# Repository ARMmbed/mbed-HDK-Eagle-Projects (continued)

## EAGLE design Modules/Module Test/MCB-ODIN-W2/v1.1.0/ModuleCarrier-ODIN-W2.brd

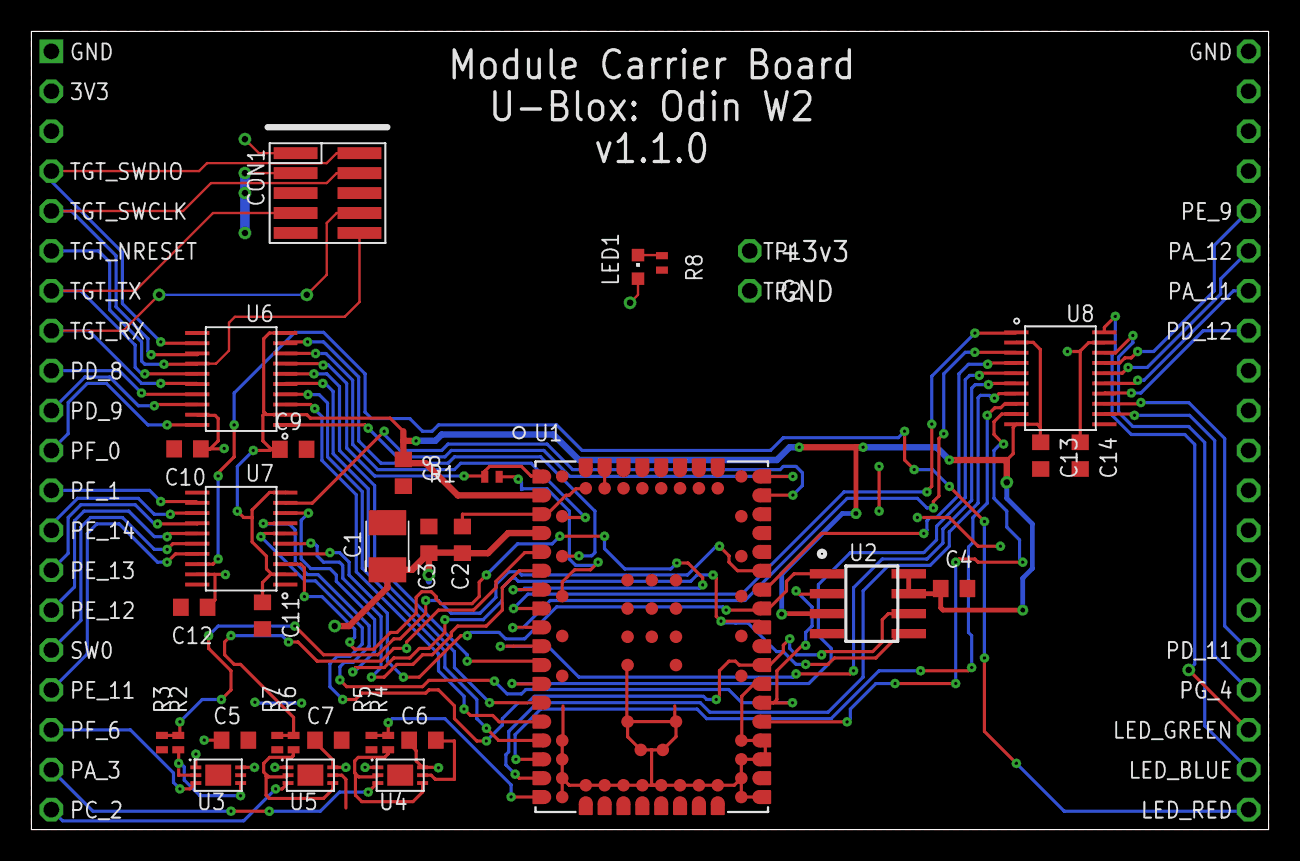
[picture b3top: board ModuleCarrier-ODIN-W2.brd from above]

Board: 2 copper layers, 78.7 x 50.8 mm, 35 parts (0 on the bottom side), 60 nets.

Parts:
C1: 10uF; SMC_B
C2, C3, C4, C5, C6, C7, C8, C9, C10, C11, C12, C13, C14: 100nF; 0603
CON1: SWD-10/TC2050_SMD; FTSH-105-02
LED1: RED; CHIPLED_0603
R1: 0; 0402
R2, R4, R6: 10K; 0402
R3, R5, R7: 12K; 0402
R8: 1k; 0402
TP1, TP2: TEST-POINT-50R-PTH; TP50-PTH
U1: ODIN-W262; ODIN-88
U2: MX25R3235FM1IH0; SO8
U3, U4, U5: LT6000IDCB#TRMPBF; 6-DFN
U6, U7, U8: TXS0108EPWR; TSSOP-20
U$1: MODULE_DAUGHTER

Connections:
1.8V: C4.2, C8.1, C9.1, C11.1, C13.1, U1.A2, U2.3, U2.7, U2.8, U6.2, U6.10, U7.2, U7.10, U8.2, U8.10
3V3-LED_BLUE: U8.18, U$1.22
3V3-LED_GREEN: U8.20, U$1.23
3V3-LED_RED: U7.18, U$1.21
3V3-PA_11: U8.15, U$1.34
3V3-PA_12: U8.16, U$1.35
3V3-PD_8: U6.17, U$1.9
3V3-PD_9: U6.18, U$1.10
3V3-PD_11: U8.13, U$1.25
3V3-PD_12: U8.14, U$1.33
3V3-PE_9: U8.17, U$1.36
3V3-PE_11: U7.17, U$1.17
3V3-PE_12: U7.15, U$1.15
3V3-PE_13: U7.14, U$1.14
3V3-PE_14: U7.13, U$1.13
3V3-PF_0: U6.20, U$1.11
3V3-PF_1: U7.12, U$1.12
3V3-PG_4: U8.12, U$1.24
3V3-SW0: U7.16, U$1.16
3V3-TGT_NRESET: CON1.10, U6.14, U$1.6
3V3-TGT_RX: CON1.8, U6.16, U$1.8
3V3-TGT_SWCLK: CON1.4, U6.13, U$1.5
3V3-TGT_SWDIO: CON1.2, U6.12, U$1.4
3V3-TGT_TX: CON1.7, U6.15, U$1.7
+3.3V: C1.+, C2.1, C3.1, C5.1, C6.1, C7.1, C10.1, C12.1, C14.1, CON1.1, LED1.A, TP1.TP, U1.A4, U3.1, U3.6, U4.1, U4.6, U5.1, U5.6, U6.19, U7.19, U8.19, U$1.2
A0_3V3: U3.3, U$1.18
A1_3V3: U4.3, U$1.19
A2_3V3: U5.3, U$1.20
GND: C1.-, C2.2, C3.2, C4.1, C5.2, C6.2, C7.2, C8.2, C9.2, C10.2, C11.2, C12.2, C13.2, C14.2, CON1.3, CON1.5, CON1.9, R3.1, R5.1, R7.1, R8.1, TP2.TP, U1.1, U1.2, U1.3, U1.4, U1.5, U1.6, U1.7, U1.8, U1.9, U1.10, U1.11, U1.12, U1.13, U1.14, U1.15, U1.16, U1.17, U1.18, U1.19, U1.20, U1.21, U1.22, U1.23, U1.24, U1.25, U1.26, U1.27, U1.28, U1.29, U1.30, U1.31, U1.32, U1.33, U1.34, U1.35, U1.36, U1.37, U1.38, U1.39, U1.A3, U1.C1, U1.C3, U1.C4, U1.C7, U1.D7, U2.4, U3.5, U3.P$7, U4.5, U4.P$7, U5.5, U5.P$7, U6.11, U7.11, U8.11, U$1.1, U$1.40
LED_BLUE: U1.A9, U8.3
LED_GREEN: U1.A8, U8.1
LED_RED: U1.A7, U7.3
unnamed: R1.2, U1.TP5
unnamed: R2.1, U3.2, U3.4
unnamed: R4.1, U4.2, U4.4
unnamed: R6.1, U5.2, U5.4
PA_1: LED1.C, R8.2
PA_3: R4.2, R5.2, U1.A18
PA_11: U1.A10, U8.6
PA_12: U1.A12, U8.5
PC_2: R6.2, R7.2, U1.A5
PD_8: U1.A15, U6.4
PD_9: U1.A14, U6.3
PD_11: U1.A16, U8.8
PD_12: U1.A17, U8.7
PE_9: U1.C12, U8.4
PE_11: U1.C11, U2.1, U7.4
PE_12: U1.C8, U2.6, U7.6
PE_13: U1.C6, U2.2, U7.7
PE_14: U1.C10, U2.5, U7.8
PF_0: U1.C18, U6.1
PF_1: U1.C17, U7.9
PF_6: R2.2, R3.2, U1.C13
PG_4: U1.C5, U8.9
SW0: U1.A6, U7.5
TGT_NRESET: R1.1, U1.A1, U6.7
TGT_RX: U1.A13, U6.5
TGT_SWCLK: U1.TP9, U6.8
TGT_SWDIO: U1.TP7, U6.9
TGT_TX: U1.A11, U6.6

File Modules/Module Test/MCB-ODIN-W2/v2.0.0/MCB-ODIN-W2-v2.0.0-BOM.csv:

"Qty";"Value";"Device";"Package";"Parts";"Description";"MF";"MFN";"OC-DIGIKEY";"OC-MOUSER";"OC-NEWARK";
"1";"0";"RESISTOR0402";"0402";"R1";"Resistor";"";"";"";"";"";
"14";"100nF";"C0603";"0603";"C2, C3, C4, C5, C6, C7, C8, C9, C10, C11, C12, C13, C14, C24";"Capacitor";"";"";"";"";"";
"3";"10K";"R0603";"0603";"R2, R4, R6";"Resistor";"";"";"";"";"";
"1";"10uF";"C-POLB";"SMC_B";"C1";"Polarised capacitor";"Kemet";"T491B106K020AT";"399-8298-1-ND";"80-T491B106K020";" 57K1740";
"3";"12K";"R0603";"0603";"R3, R5, R7";"Resistor";"";"";"";"";"";
"1";"1k";"R0603";"0603";"R8";"Resistor";"";"";"";"";"";
"2";"4k7";"R0603";"0603";"R10, R11";"Resistor";"";"";"";"";"";
"1";"ATECC608A";"ATECC608A";"SO8";"IC3";"I2C Secure element and crytpo accelerator";"Atmel";"ATECC608A";"ATECC608A-SSHDA-TCT-ND ";"556-ATECC608ASSHDAB ";"";
"1";"GREEN";"SMD_LED0603";"CHIPLED_0603";"LED1";"LED SMD, Colour Red";"Wurth Electronics Inc";"150060RS75000";"732-4978-1-ND";"710-150060RS75000";"2322071";
"3";"LT6000IDCB#TRMPBF";"LT6000IDCB#TRMPBF";"6-DFN";"U3, U4, U5";"IC OPAMP GBP 60KHZ RRO 6DFN";"Linear Technology";"LT6000IDCB#TRMPBF";"LT6000IDCB#TRMPBFCT-ND";"";"95M6567";
"1";"MODULE_DAUGHTER";"MODULE_DAUGHTER";"MODULE_DAUGHTER";"MOD1";"";"";"";"";"";"";
"1";"MX25R3235FM1IH0";"MX25R3235FM1IH0";"SO8";"U2";"Serial Flash 32 Mb 80 Mhz";"Macronix";"MX25R3235FM2IH0";"1092-1174-ND";"";"";
"1";"ODIN-W262";"ODIN-W262";"ODIN-88";"U1";"ODIN-W260: Host-based multiradio module with";"";"";"";"";"";
"1";"SWD-10/TC2050_SMD";"SWD-10/TC2050_SMD";"FTSH-105-02";"CON1";"1mm pitch 10-Pin Cortex Programming Header with optional TC2050 footprint solderless interchangeable";"";"";"";"";"";
"2";"TEST_POINT-50R-PTH";"TEST_POINT-50R-PTH";"TP50-PTH";"TP1, TP2";"";"";"";"";"";"";
"3";"TXS0108EPWR";"TXS0108EPWR";"TSSOP-20";"U6, U7, U8";"8-Bit Bi-directional, Level-Shifting, Voltage Translator";"Texas Instruments";"TXS0108EPWR";"296-23011-1-ND";"595-TXS0108EPWR";"05R8300";

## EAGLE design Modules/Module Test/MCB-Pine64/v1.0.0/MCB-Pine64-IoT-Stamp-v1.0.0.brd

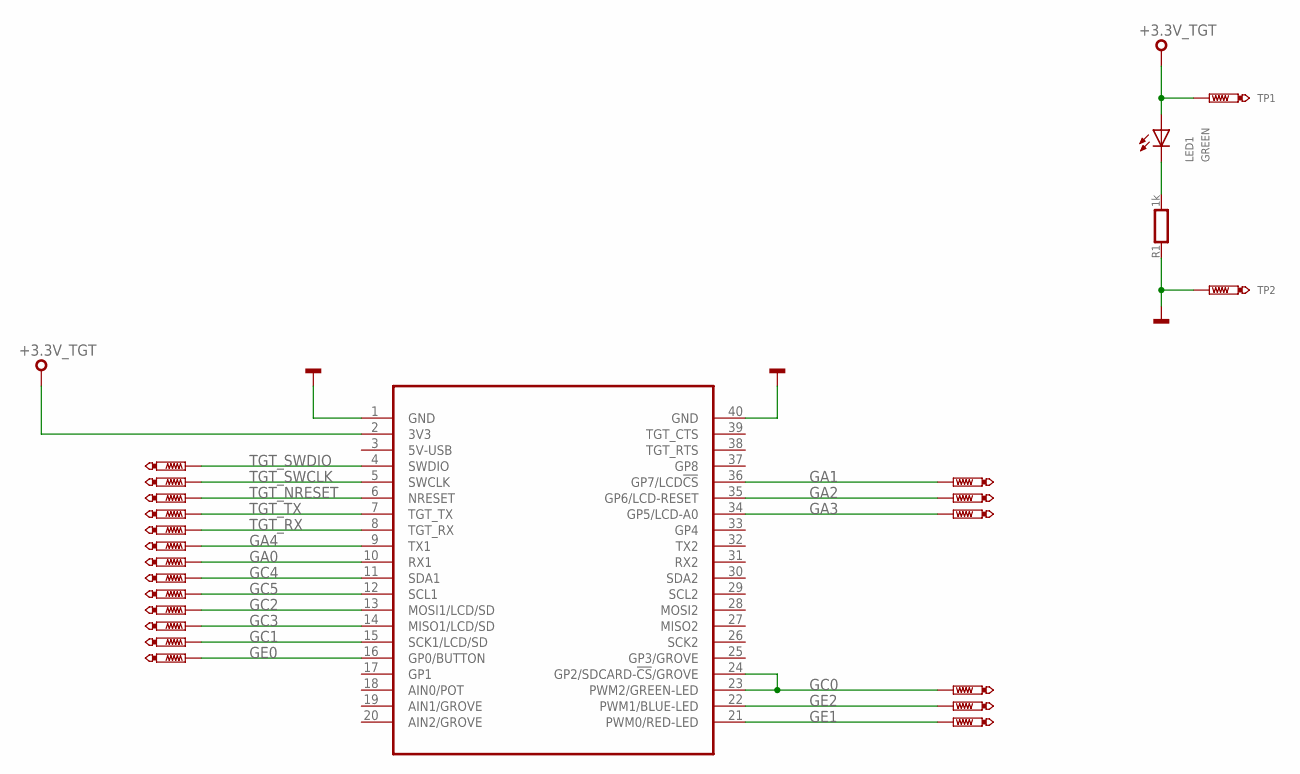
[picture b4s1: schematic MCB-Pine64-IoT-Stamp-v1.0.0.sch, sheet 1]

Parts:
LED1: GREEN; CHIPLED_0603
MOD1: MODULE_DAUGHTER
R1: 1k; 0603
TP1, TP2: TEST-POINT-50R-PTH; TP50-PTH
TP3, TP4, TP7, TP8, TP9, TP13, TP14, TP15, TP17, TP19, TP20, TP21, TP22, TP25, TP26, TP27, TP28, TP29, TP30: PTR1TP07R; TP07R

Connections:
+3.3V_TGT: LED1.A, MOD1.2 (3V3), TP1.TP; also elsewhere on the board
GA0: MOD1.10 (RX1), TP21.TP; also elsewhere on the board
GA1: MOD1.36 (GP7/LCD!CS), TP25.TP; also elsewhere on the board
GA2: MOD1.35 (GP6/LCD-RESET), TP20.TP; also elsewhere on the board
GA3: MOD1.34 (GP5/LCD-A0), TP19.TP; also elsewhere on the board
GA4: MOD1.9 (TX1), TP22.TP; also elsewhere on the board
GC0: MOD1.23 (PWM2/GREEN-LED), MOD1.24 (GP2/SDCARD-!CS!/GROVE), TP15.TP; also elsewhere on the board
GC1: MOD1.15 (SCK1/LCD/SD), TP9.TP; also elsewhere on the board
GC2: MOD1.13 (MOSI1/LCD/SD), TP7.TP; also elsewhere on the board
GC3: MOD1.14 (MISO1/LCD/SD), TP8.TP; also elsewhere on the board
GC4: MOD1.11 (SDA1), TP3.TP; also elsewhere on the board
GC5: MOD1.12 (SCL1), TP4.TP; also elsewhere on the board
GE0: MOD1.16 (GP0/BUTTON), TP17.TP; also elsewhere on the board
GE1: MOD1.21 (PWM0/RED-LED), TP13.TP; also elsewhere on the board
GE2: MOD1.22 (PWM1/BLUE-LED), TP14.TP; also elsewhere on the board
GND: MOD1.1 (GND), MOD1.40 (GND), R1.1, TP2.TP; also elsewhere on the board
PA_1: LED1.C, R1.2
TGT_NRESET: MOD1.6 (NRESET), TP28.TP; also elsewhere on the board
TGT_RX: MOD1.8 (TGT_RX), TP30.TP; also elsewhere on the board
TGT_SWCLK: MOD1.5 (SWCLK), TP27.TP; also elsewhere on the board
TGT_SWDIO: MOD1.4 (SWDIO), TP26.TP; also elsewhere on the board
TGT_TX: MOD1.7 (TGT_TX), TP29.TP; also elsewhere on the board

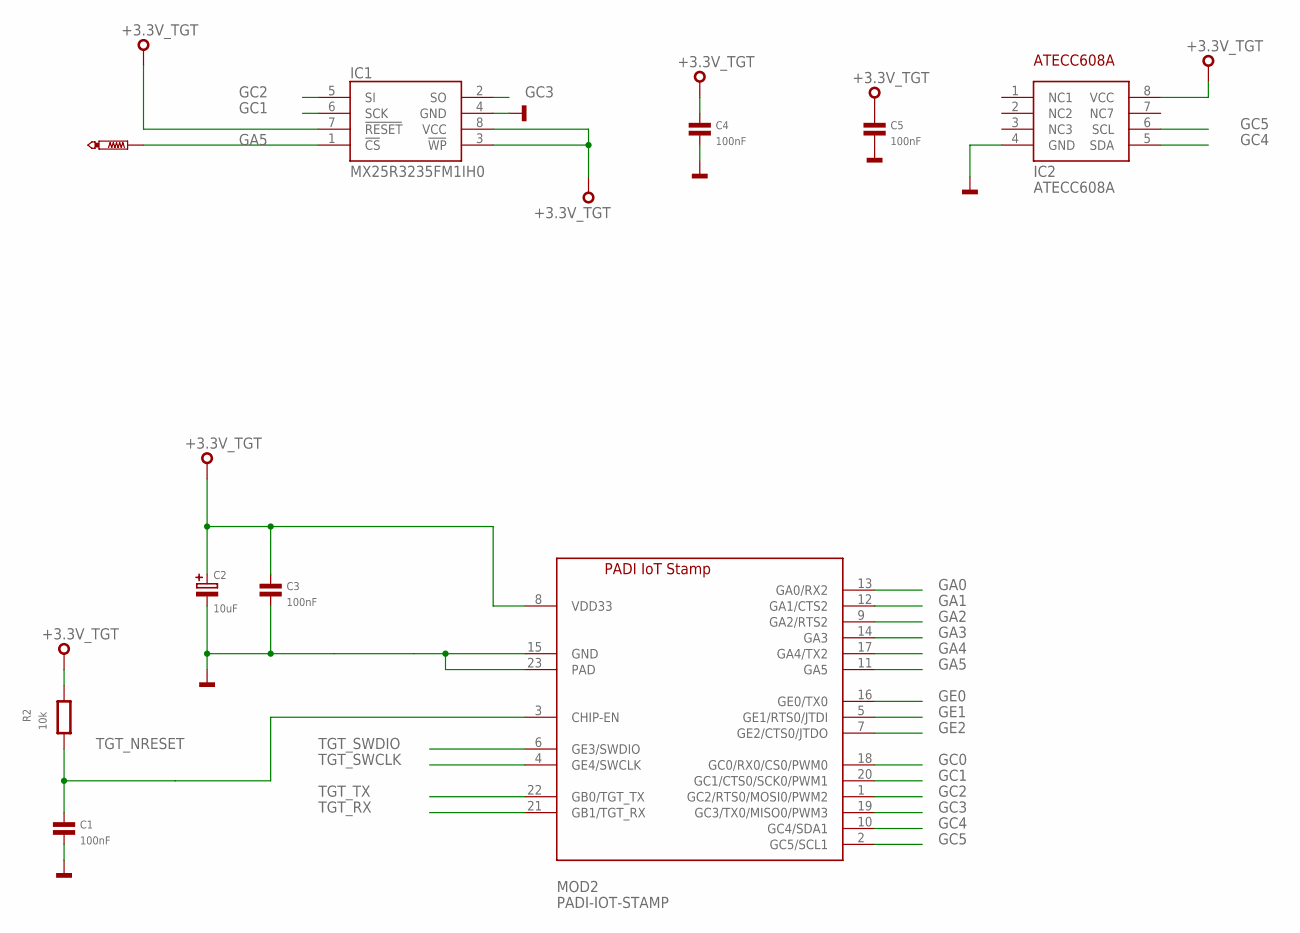
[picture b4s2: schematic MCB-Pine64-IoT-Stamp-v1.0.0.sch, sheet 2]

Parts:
C1, C3, C4, C5: 100nF; 0603
C2: 10uF; SMC_B
IC1: MX25R3235FM1IH0; SO8
IC2: ATECC608A; SO8
MOD2: PADI-IOT-STAMP
R2: 10k; 0603
TP5: PTR1TP07R; TP07R

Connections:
+3.3V_TGT: C2.+, C3.1, C4.1, C5.1, IC1.3 (!WP), IC1.7 (!RESET), IC1.8 (VCC), IC2.8 (VCC), MOD2.8 (VDD33), R2.2; also elsewhere on the board
GA0: MOD2.13 (GA0/RX2); also elsewhere on the board
GA1: MOD2.12 (GA1/CTS2); also elsewhere on the board
GA2: MOD2.9 (GA2/RTS2); also elsewhere on the board
GA3: MOD2.14 (GA3); also elsewhere on the board
GA4: MOD2.17 (GA4/TX2); also elsewhere on the board
GA5: IC1.1 (!CS), MOD2.11 (GA5), TP5.TP
GC0: MOD2.18 (GC0/RX0/CS0/PWM0); also elsewhere on the board
GC1: IC1.6 (SCK), MOD2.20 (GC1/CTS0/SCK0/PWM1); also elsewhere on the board
GC2: IC1.5 (SI), MOD2.1 (GC2/RTS0/MOSI0/PWM2); also elsewhere on the board
GC3: IC1.2 (SO), MOD2.19 (GC3/TX0/MISO0/PWM3); also elsewhere on the board
GC4: IC2.5 (SDA), MOD2.10 (GC4/SDA1); also elsewhere on the board
GC5: IC2.6 (SCL), MOD2.2 (GC5/SCL1); also elsewhere on the board
GE0: MOD2.16 (GE0/TX0); also elsewhere on the board
GE1: MOD2.5 (GE1/RTS0/JTDI); also elsewhere on the board
GE2: MOD2.7 (GE2/CTS0/JTDO); also elsewhere on the board
GND: C1.2, C2.-, C3.2, C4.2, C5.2, IC1.4 (GND), IC2.4 (GND), MOD2.15 (GND), MOD2.23 (PAD); also elsewhere on the board
TGT_NRESET: C1.1, MOD2.3 (CHIP-EN), R2.1; also elsewhere on the board
TGT_RX: MOD2.21 (GB1/TGT_RX); also elsewhere on the board
TGT_SWCLK: MOD2.4 (GE4/SWCLK); also elsewhere on the board
TGT_SWDIO: MOD2.6 (GE3/SWDIO); also elsewhere on the board
TGT_TX: MOD2.22 (GB0/TGT_TX); also elsewhere on the board

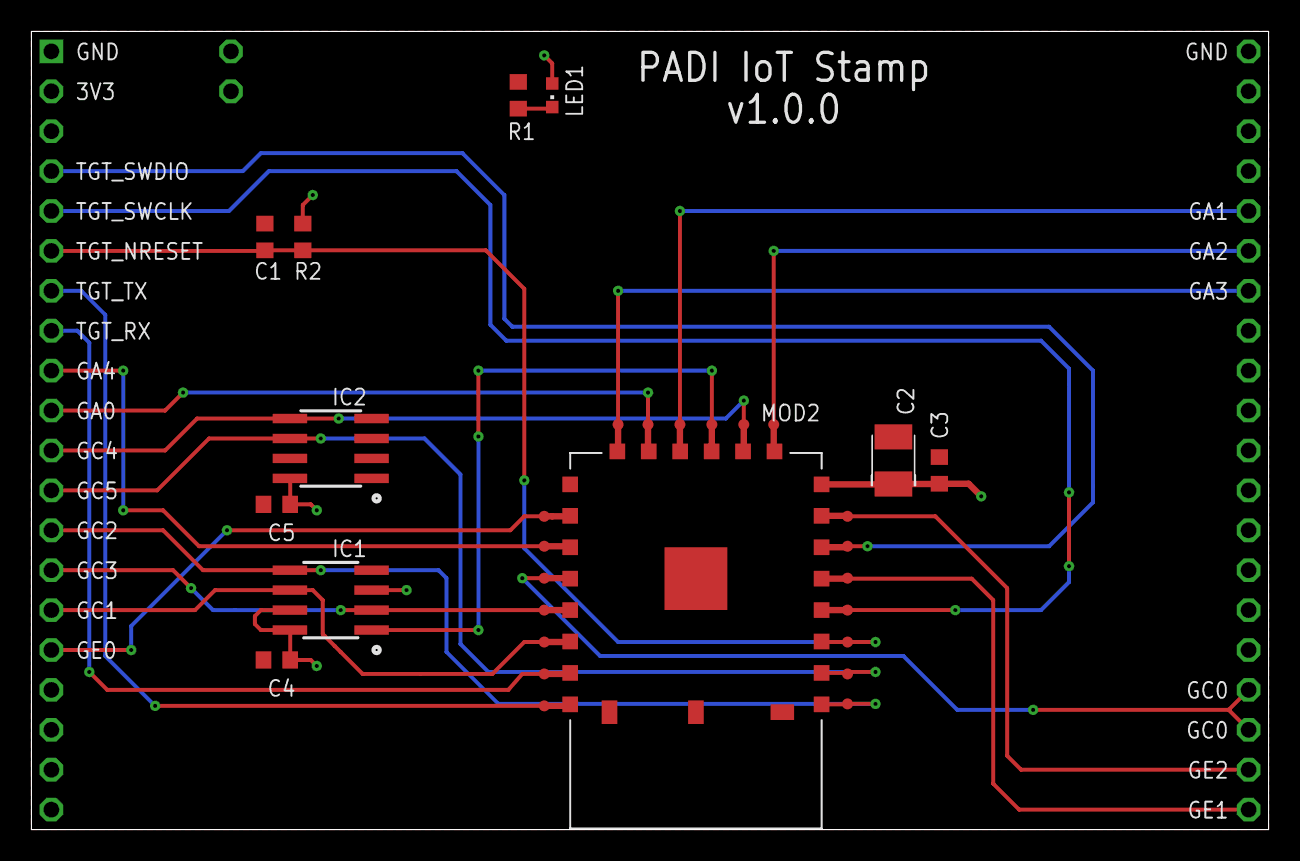
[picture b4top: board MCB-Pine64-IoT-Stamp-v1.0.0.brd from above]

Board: 2 copper layers, 78.7 x 50.8 mm, 35 parts (0 on the bottom side), 23 nets.

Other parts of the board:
SS2: FLOSSICORN0.25; FLOSSICORN-0.25

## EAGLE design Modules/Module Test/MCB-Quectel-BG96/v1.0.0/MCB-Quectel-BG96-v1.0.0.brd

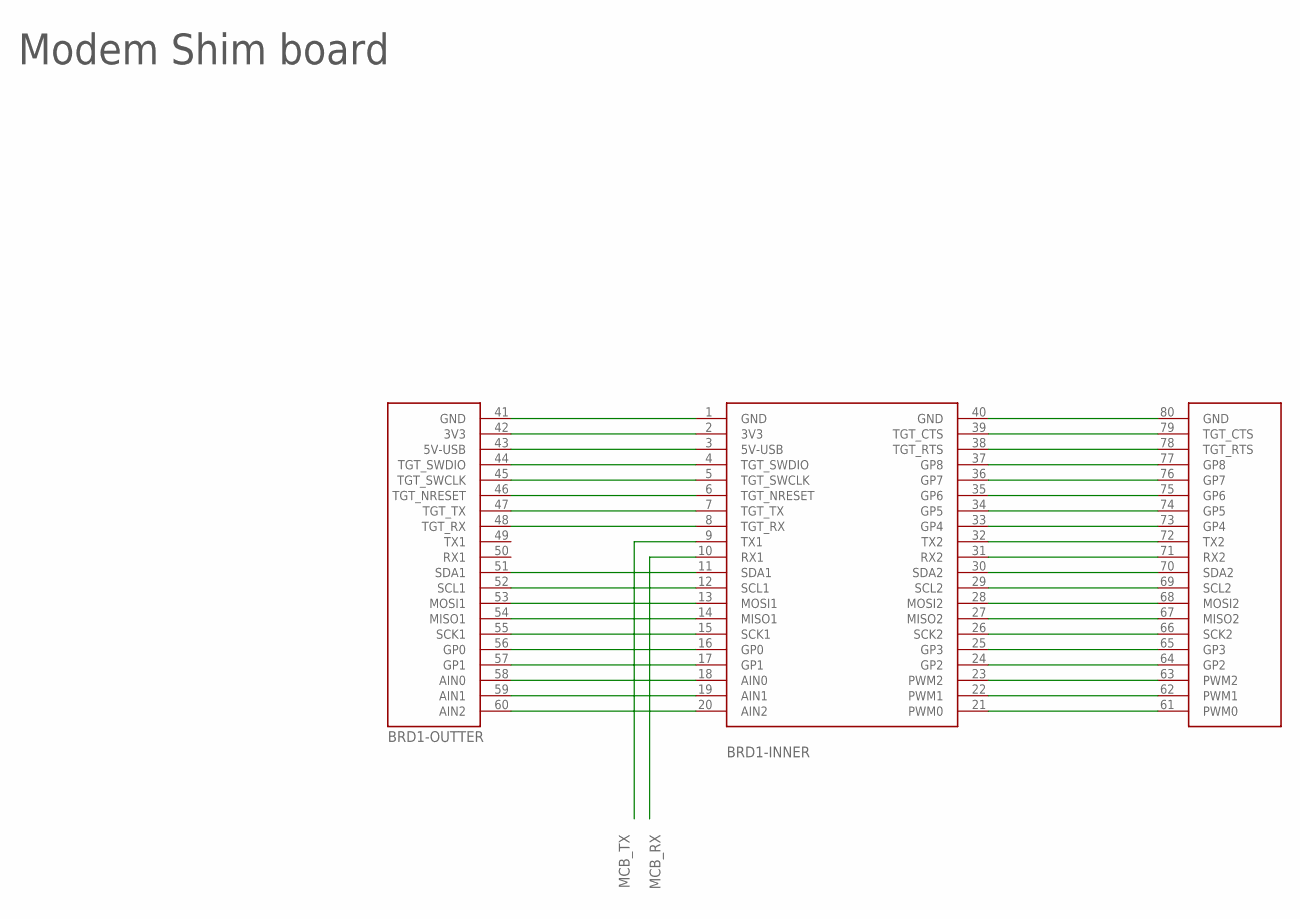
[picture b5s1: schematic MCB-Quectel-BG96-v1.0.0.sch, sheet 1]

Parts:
BRD1: MODULE-SHIM-BRD; MODULE-SHIM-BOARD

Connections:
MCB_RX: BRD1.10 (RX1)
MCB_TX: BRD1.9 (TX1)
unnamed: BRD1.40 (GND), BRD1.80 (GND)
unnamed: BRD1.39 (TGT_CTS), BRD1.79 (TGT_CTS)
unnamed: BRD1.38 (TGT_RTS), BRD1.78 (TGT_RTS)
unnamed: BRD1.37 (GP8), BRD1.77 (GP8)
unnamed: BRD1.36 (GP7), BRD1.76 (GP7)
unnamed: BRD1.35 (GP6), BRD1.75 (GP6)
unnamed: BRD1.34 (GP5), BRD1.74 (GP5)
unnamed: BRD1.33 (GP4), BRD1.73 (GP4)
unnamed: BRD1.32 (TX2), BRD1.72 (TX2)
unnamed: BRD1.31 (RX2), BRD1.71 (RX2)
unnamed: BRD1.30 (SDA2), BRD1.70 (SDA2)
unnamed: BRD1.29 (SCL2), BRD1.69 (SCL2)
unnamed: BRD1.28 (MOSI2), BRD1.68 (MOSI2)
unnamed: BRD1.27 (MISO2), BRD1.67 (MISO2)
unnamed: BRD1.26 (SCK2), BRD1.66 (SCK2)
unnamed: BRD1.25 (GP3), BRD1.65 (GP3)
unnamed: BRD1.24 (GP2), BRD1.64 (GP2)
unnamed: BRD1.23 (PWM2), BRD1.63 (PWM2)
unnamed: BRD1.22 (PWM1), BRD1.62 (PWM1)
unnamed: BRD1.21 (PWM0), BRD1.61 (PWM0)
unnamed: BRD1.1 (GND), BRD1.41 (GND)
unnamed: BRD1.2 (3V3), BRD1.42 (3V3)
unnamed: BRD1.3 (5V-USB), BRD1.43 (5V-USB)
unnamed: BRD1.4 (TGT_SWDIO), BRD1.44 (TGT_SWDIO)
unnamed: BRD1.5 (TGT_SWCLK), BRD1.45 (TGT_SWCLK)
unnamed: BRD1.6 (TGT_NRESET), BRD1.46 (TGT_NRESET)
unnamed: BRD1.7 (TGT_TX), BRD1.47 (TGT_TX)
unnamed: BRD1.8 (TGT_RX), BRD1.48 (TGT_RX)
unnamed: BRD1.11 (SDA1), BRD1.51 (SDA1)
unnamed: BRD1.12 (SCL1), BRD1.52 (SCL1)
unnamed: BRD1.13 (MOSI1), BRD1.53 (MOSI1)
unnamed: BRD1.14 (MISO1), BRD1.54 (MISO1)
unnamed: BRD1.15 (SCK1), BRD1.55 (SCK1)
unnamed: BRD1.16 (GP0), BRD1.56 (GP0)
unnamed: BRD1.17 (GP1), BRD1.57 (GP1)
unnamed: BRD1.18 (AIN0), BRD1.58 (AIN0)
unnamed: BRD1.19 (AIN1), BRD1.59 (AIN1)
unnamed: BRD1.20 (AIN2), BRD1.60 (AIN2)

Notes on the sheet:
Modem Shim board

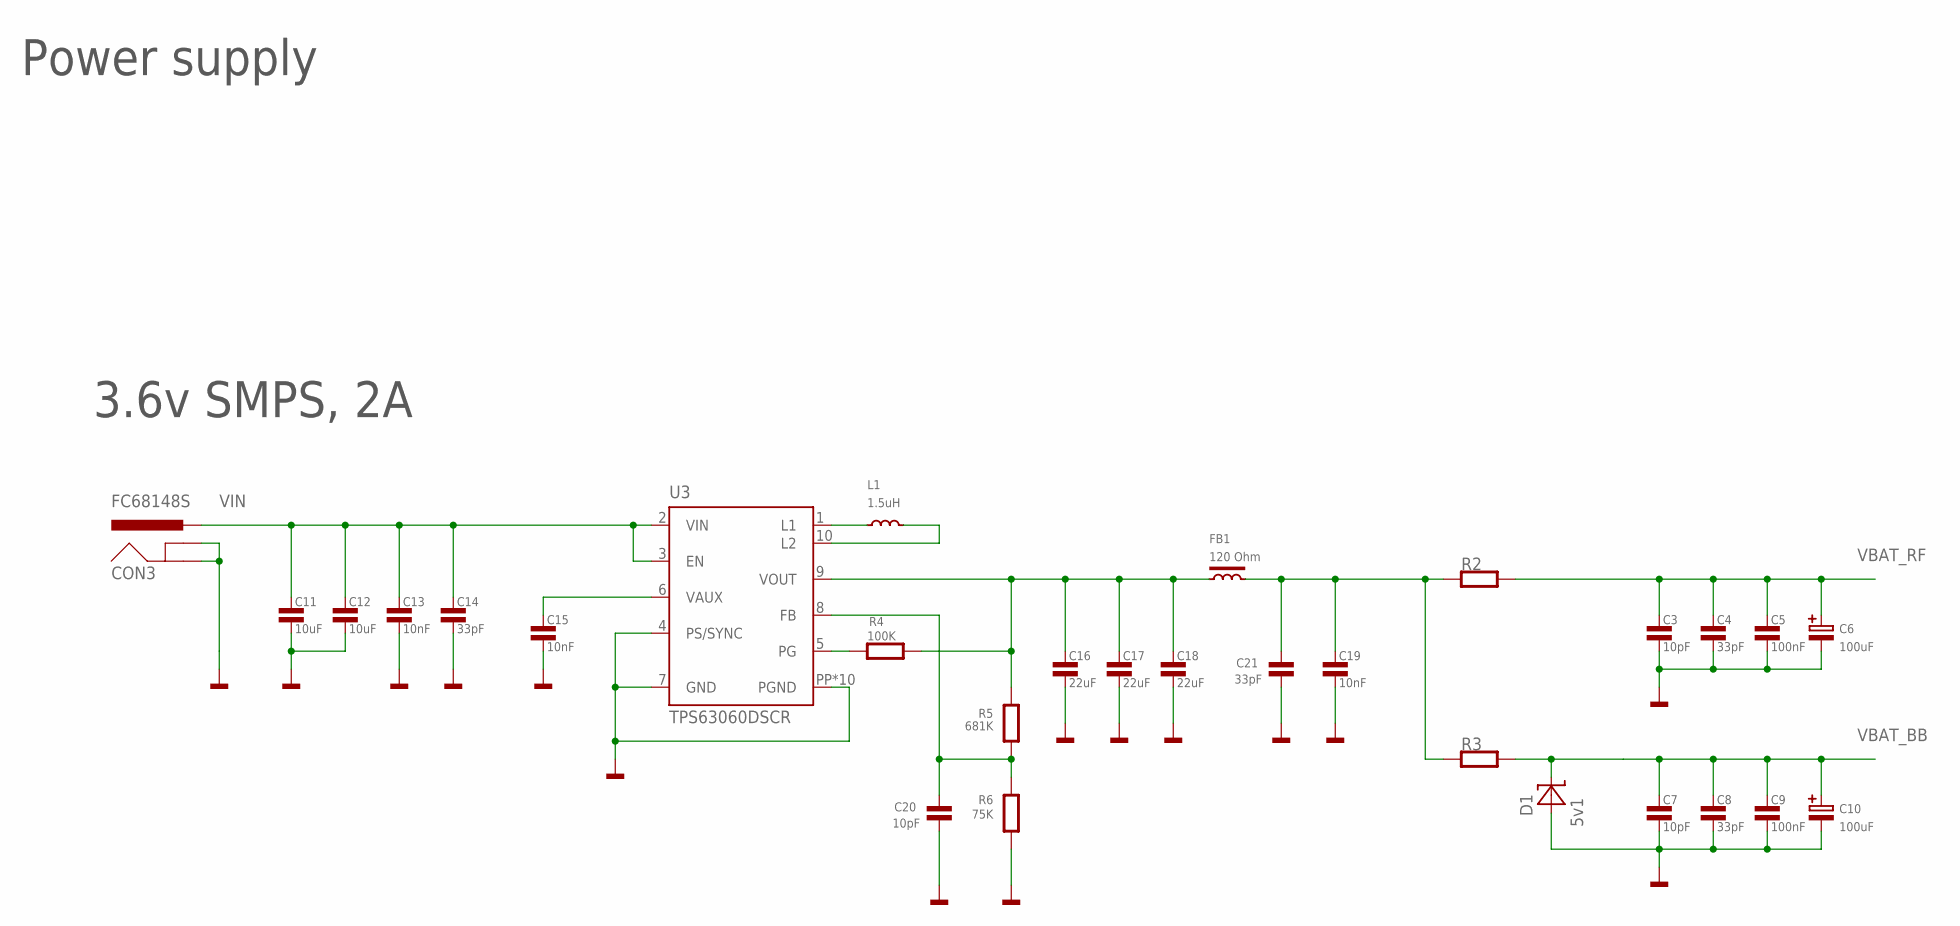
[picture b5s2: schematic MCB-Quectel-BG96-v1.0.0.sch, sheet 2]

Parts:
C3, C7, C20: 10pF; 0603
C4, C8, C14, C21: 33pF; 0603
C5, C9: 100nF; 0603
C6, C10: 100uF; SMC_A
C11, C12: 10uF; 0603
C13, C15, C19: 10nF; 0603
C16, C17, C18: 22uF; 0603
CON3: FC68148S
D1: 5v1; SOD123
FB1: 120 Ohm; 0603
L1: 1.5uH; XFL4020-472MEC
R2, R3: R0603; 0603
R4: 100K; 0603
R5: 681K; 0603
R6: 75K; 0603
U3: TPS63060DSCR; DSC-S-PWSON-N10

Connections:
GND: C3.2, C4.2, C5.2, C6.-, C7.2, C8.2, C9.2, C10.-, C11.2, C12.2, C13.2, C14.2, C15.2, C16.2, C17.2, C18.2, C19.2, C20.2, C21.2, CON3.2 (GNDBREAK), CON3.3 (GND), D1.1 (A), R6.1, U3.4 (PS/SYNC), U3.7 (GND), U3.PP (PGND), U3.PP@1 (PGND), U3.PP@2 (PGND), U3.PP@3 (PGND), U3.PP@4 (PGND), U3.PP@5 (PGND), U3.PP@7 (PGND), U3.PP@8 (PGND), U3.PP@9 (PGND), U3.PP@10 (PGND); also elsewhere on the board
unnamed: C15.1, U3.6 (VAUX)
unnamed: C19.1, C21.1, FB1.2, R2.1, R3.1
unnamed: L1.P$1, U3.1 (L1)
unnamed: L1.P$2, U3.10 (L2)
unnamed: C16.1, C17.1, C18.1, FB1.1, R4.2, R5.2, U3.9 (VOUT)
unnamed: R4.1, U3.5 (PG)
unnamed: C20.1, R5.1, R6.2, U3.8 (FB)
VBAT_BB: C7.1, C8.1, C9.1, C10.+, D1.2 (C), R3.2; also elsewhere on the board
VBAT_RF: C3.1, C4.1, C5.1, C6.+, R2.2; also elsewhere on the board
VIN: C11.1, C12.1, C13.1, C14.1, CON3.1-1 (PWR), CON3.1-2 (PWR), U3.2 (VIN), U3.3 (EN)

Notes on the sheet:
Power supply
3.6v SMPS, 2A

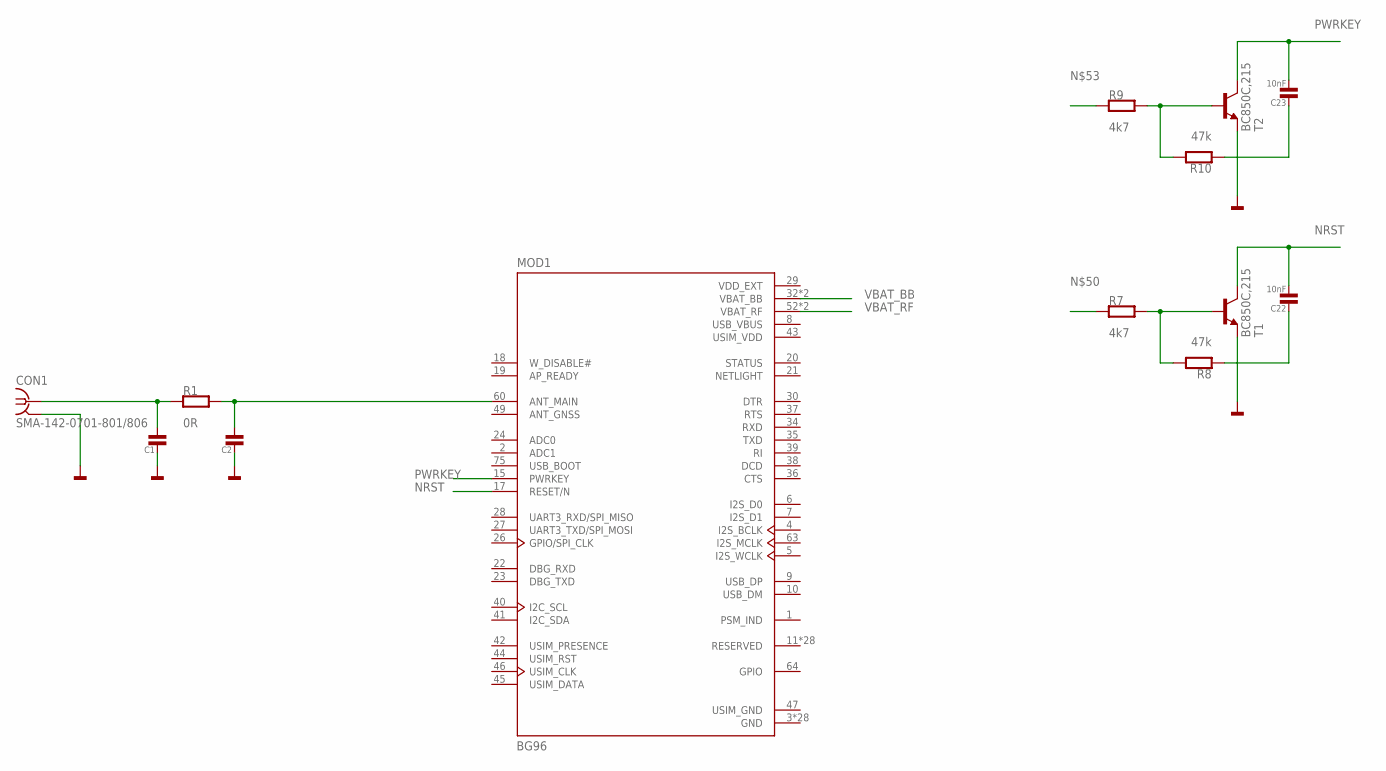
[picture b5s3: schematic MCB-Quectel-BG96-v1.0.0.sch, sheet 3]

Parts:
C1, C2: C0603; 0603
C22, C23: 10nF; 0603
CON1: SMA-142-0701-801/806; J502-ND-142-0701-801/806
MOD1: BG96; LTE_MODULE_BG96
R1: 0R; 0603
R7, R9: 4k7; 0603
R8, R10: 47k; 0603
T1, T2: BC850C,215; SOT23-3

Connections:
GND: C1.1, C2.1, C22.1, C23.1, CON1.G@1 (2), CON1.G@2 (2), CON1.G@3 (2), CON1.G@4 (2), MOD1.3 (GND), MOD1.31 (GND), MOD1.48 (GND), MOD1.50 (GND), MOD1.54 (GND), MOD1.55 (GND), MOD1.58 (GND), MOD1.59 (GND), MOD1.61 (GND), MOD1.62 (GND), MOD1.67 (GND), MOD1.68 (GND), MOD1.69 (GND), MOD1.70 (GND), MOD1.71 (GND), MOD1.72 (GND), MOD1.73 (GND), MOD1.74 (GND), MOD1.79 (GND), MOD1.80 (GND), MOD1.81 (GND), MOD1.82 (GND), MOD1.89 (GND), MOD1.90 (GND), MOD1.91 (GND), MOD1.100 (GND), MOD1.101 (GND), MOD1.102 (GND), R8.1, R10.1, T1.2 (E), T2.2 (E); also elsewhere on the board
unnamed: C1.2, CON1.1, R1.1
unnamed: C2.2, MOD1.60 (ANT_MAIN), R1.2
unnamed: R7.2, R8.2, T1.1 (B)
unnamed: R9.2, R10.2, T2.1 (B)
NRST: C22.2, MOD1.17 (RESET/N), T1.3 (C)
PWRKEY: C23.2, MOD1.15 (PWRKEY), T2.3 (C)
USB_VBUS: MOD1.8 (USB_VBUS)
USIM_GND: MOD1.47 (USIM_GND)
USIM_VDD: MOD1.43 (USIM_VDD)
VBAT_BB: MOD1.32 (VBAT_BB), MOD1.33 (VBAT_BB); also elsewhere on the board
VBAT_RF: MOD1.52 (VBAT_RF), MOD1.53 (VBAT_RF); also elsewhere on the board
VDD_EXT: MOD1.29 (VDD_EXT)

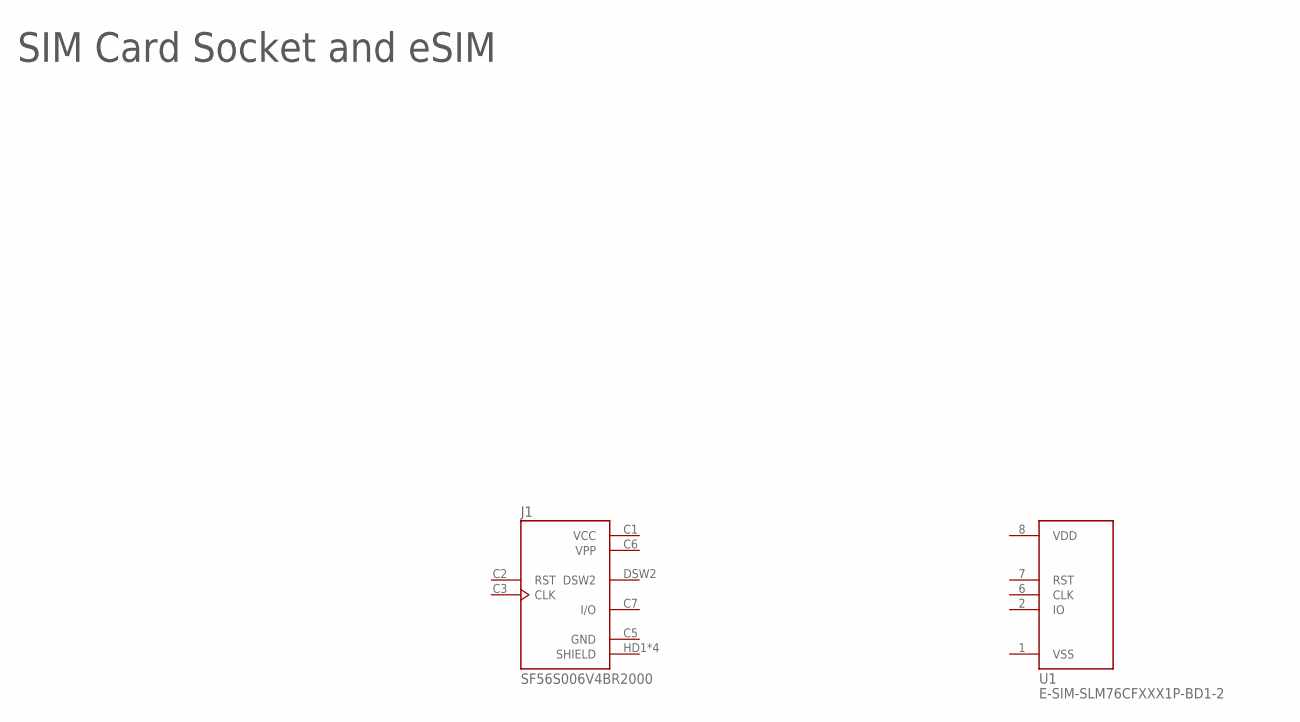
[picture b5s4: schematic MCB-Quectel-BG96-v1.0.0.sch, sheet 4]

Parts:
J1: SF56S006V4BR2000; JAE_SF56S006V4BR2000
U1: E-SIM-SLM76CFXXX1P-BD1-2; VQFN-8-1

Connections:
GND: J1.C5 (GND); also elsewhere on the board
SHIELD: J1.HD1 (SHIELD), J1.HD2,DSW1 (SHIELD), J1.HD3 (SHIELD), J1.HD4 (SHIELD)
VCC: J1.C1 (VCC)
VPP: J1.C6 (VPP)

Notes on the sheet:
SIM Card Socket and eSIM

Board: 2 copper layers, 45 parts (0 on the bottom side), 56 nets, no tracks yet.

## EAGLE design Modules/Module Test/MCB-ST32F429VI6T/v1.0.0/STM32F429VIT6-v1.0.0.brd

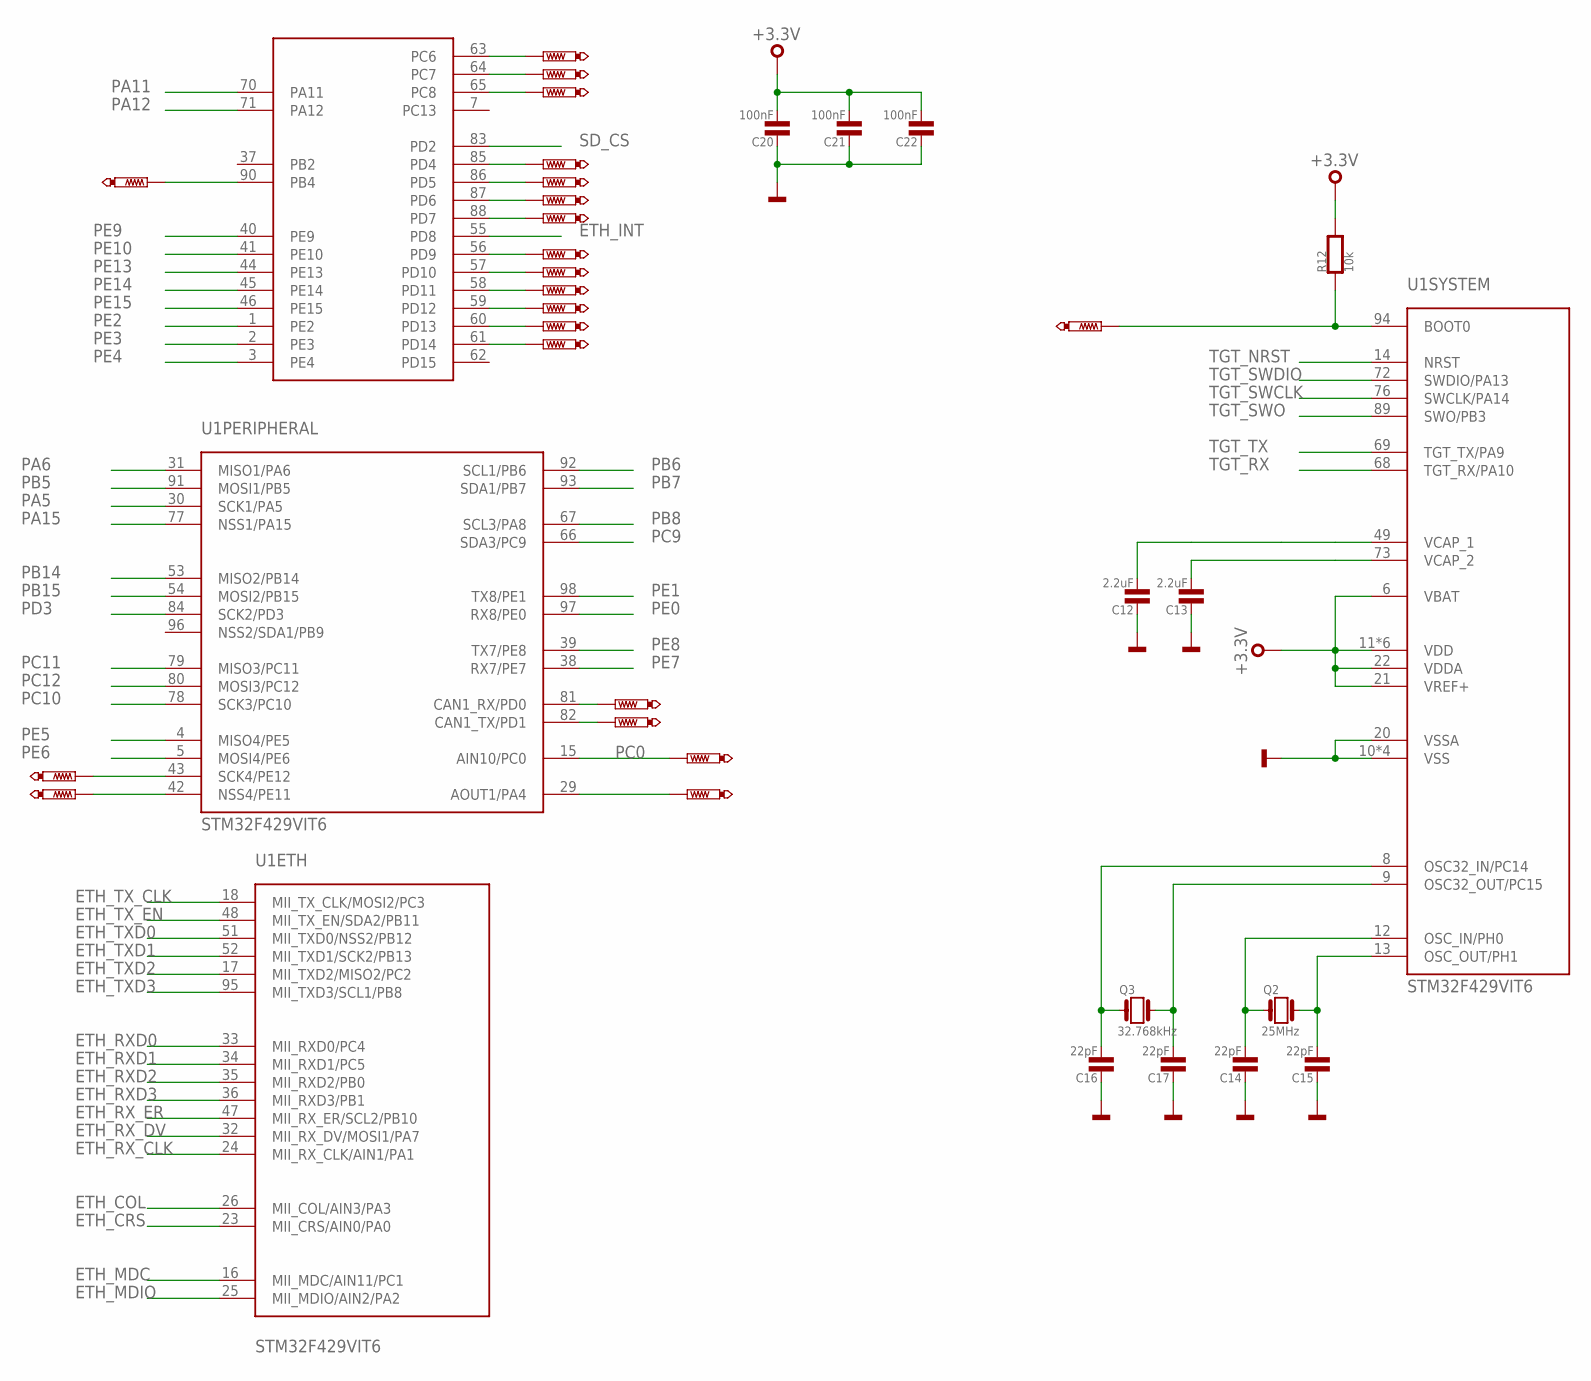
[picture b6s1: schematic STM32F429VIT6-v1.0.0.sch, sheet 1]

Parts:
C12, C13: 2.2uF; 0402
C14, C15, C16, C17: 22pF; 0603
C20, C21, C22: 100nF; 0402
Q2: 25MHz; 3.2X.2.5
Q3: 32.768kHz; FC135
R12: 10k; 0402
TP3, TP4, TP5, TP6, TP7, TP8, TP9, TP10, TP11, TP12, TP13, TP15, TP16, TP17, TP18, TP19, TP20, TP21, TP22, TP23, TP24: PTR1TP06R; TP06R
U1: STM32F429VIT6; QFP50P1600X1600X160-100N

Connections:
+3.3V: C20.2, C21.2, C22.2, R12.2, U1.6 (VBAT), U1.11 (VDD), U1.19 (VDD), U1.21 (VREF+), U1.22 (VDDA), U1.28 (VDD), U1.50 (VDD), U1.75 (VDD), U1.100 (VDD); also elsewhere on the board
ETH_COL: U1.26 (MII_COL/AIN3/PA3); also elsewhere on the board
ETH_CRS: U1.23 (MII_CRS/AIN0/PA0); also elsewhere on the board
ETH_INT: U1.55 (PD8); also elsewhere on the board
ETH_MDC: U1.16 (MII_MDC/AIN11/PC1); also elsewhere on the board
ETH_MDIO: U1.25 (MII_MDIO/AIN2/PA2); also elsewhere on the board
ETH_RXD0: U1.33 (MII_RXD0/PC4); also elsewhere on the board
ETH_RXD1: U1.34 (MII_RXD1/PC5); also elsewhere on the board
ETH_RXD2: U1.35 (MII_RXD2/PB0); also elsewhere on the board
ETH_RXD3: U1.36 (MII_RXD3/PB1); also elsewhere on the board
ETH_RX_CLK: U1.24 (MII_RX_CLK/AIN1/PA1); also elsewhere on the board
ETH_RX_DV: U1.32 (MII_RX_DV/MOSI1/PA7); also elsewhere on the board
ETH_RX_ER: U1.47 (MII_RX_ER/SCL2/PB10); also elsewhere on the board
ETH_TXD0: U1.51 (MII_TXD0/NSS2/PB12); also elsewhere on the board
ETH_TXD1: U1.52 (MII_TXD1/SCK2/PB13); also elsewhere on the board
ETH_TXD2: U1.17 (MII_TXD2/MISO2/PC2); also elsewhere on the board
ETH_TXD3: U1.95 (MII_TXD3/SCL1/PB8); also elsewhere on the board
ETH_TX_CLK: U1.18 (MII_TX_CLK/MOSI2/PC3); also elsewhere on the board
ETH_TX_EN: U1.48 (MII_TX_EN/SDA2/PB11); also elsewhere on the board
GND: C12.1, C13.1, C14.1, C15.1, C16.1, C17.1, C20.1, C21.1, C22.1, U1.10 (VSS), U1.20 (VSSA), U1.27 (VSS), U1.74 (VSS), U1.99 (VSS); also elsewhere on the board
unnamed: R12.1, TP6.TP, U1.94 (BOOT0)
unnamed: TP3.TP, U1.81 (CAN1_RX/PD0)
unnamed: C12.2, U1.49 (VCAP_1)
unnamed: C14.2, Q2.P$1 (1), U1.12 (OSC_IN/PH0)
unnamed: C15.2, Q2.P$3 (2), U1.13 (OSC_OUT/PH1)
unnamed: C17.2, Q3.X2 (2), U1.9 (OSC32_OUT/PC15)
unnamed: C13.2, U1.73 (VCAP_2)
unnamed: C16.2, Q3.X1 (1), U1.8 (OSC32_IN/PC14)
unnamed: TP4.TP, U1.82 (CAN1_TX/PD1)
unnamed: TP7.TP, U1.29 (AOUT1/PA4)
unnamed: TP8.TP, U1.42 (NSS4/PE11)
unnamed: TP9.TP, U1.43 (SCK4/PE12)
unnamed: TP18.TP, U1.88 (PD7)
unnamed: TP11.TP, U1.90 (PB4)
unnamed: TP21.TP, U1.85 (PD4)
unnamed: TP20.TP, U1.86 (PD5)
unnamed: TP19.TP, U1.87 (PD6)
unnamed: TP17.TP, U1.65 (PC8)
unnamed: TP16.TP, U1.64 (PC7)
unnamed: TP15.TP, U1.63 (PC6)
unnamed: TP12.TP, U1.60 (PD13)
unnamed: TP13.TP, U1.56 (PD9)
unnamed: TP10.TP, U1.57 (PD10)
unnamed: TP22.TP, U1.58 (PD11)
unnamed: TP23.TP, U1.59 (PD12)
unnamed: TP24.TP, U1.61 (PD14)
PA5: U1.30 (SCK1/PA5); also elsewhere on the board
PA6: U1.31 (MISO1/PA6); also elsewhere on the board
PA11: U1.70 (PA11); also elsewhere on the board
PA12: U1.71 (PA12); also elsewhere on the board
PA15: U1.77 (NSS1/PA15); also elsewhere on the board
PB5: U1.91 (MOSI1/PB5); also elsewhere on the board
PB6: U1.92 (SCL1/PB6); also elsewhere on the board
PB7: U1.93 (SDA1/PB7); also elsewhere on the board
PB8: U1.67 (SCL3/PA8); also elsewhere on the board
PB14: U1.53 (MISO2/PB14); also elsewhere on the board
PB15: U1.54 (MOSI2/PB15); also elsewhere on the board
PC0: TP5.TP, U1.15 (AIN10/PC0); also elsewhere on the board
PC9: U1.66 (SDA3/PC9); also elsewhere on the board
PC10: U1.78 (SCK3/PC10); also elsewhere on the board
PC11: U1.79 (MISO3/PC11); also elsewhere on the board
PC12: U1.80 (MOSI3/PC12); also elsewhere on the board
PD3: U1.84 (SCK2/PD3); also elsewhere on the board
PE0: U1.97 (RX8/PE0); also elsewhere on the board
PE1: U1.98 (TX8/PE1); also elsewhere on the board
PE2: U1.1 (PE2); also elsewhere on the board
PE3: U1.2 (PE3); also elsewhere on the board
PE4: U1.3 (PE4); also elsewhere on the board
PE5: U1.4 (MISO4/PE5); also elsewhere on the board
PE6: U1.5 (MOSI4/PE6); also elsewhere on the board
PE7: U1.38 (RX7/PE7); also elsewhere on the board
PE8: U1.39 (TX7/PE8); also elsewhere on the board
PE9: U1.40 (PE9); also elsewhere on the board
PE10: U1.41 (PE10); also elsewhere on the board
PE13: U1.44 (PE13); also elsewhere on the board
PE14: U1.45 (PE14); also elsewhere on the board
PE15: U1.46 (PE15); also elsewhere on the board
SD_CS: U1.83 (PD2); also elsewhere on the board
TGT_NRST: U1.14 (NRST); also elsewhere on the board
TGT_RX: U1.68 (TGT_RX/PA10); also elsewhere on the board
TGT_SWCLK: U1.76 (SWCLK/PA14); also elsewhere on the board
TGT_SWDIO: U1.72 (SWDIO/PA13); also elsewhere on the board
TGT_SWO: U1.89 (SWO/PB3); also elsewhere on the board
TGT_TX: U1.69 (TGT_TX/PA9); also elsewhere on the board
